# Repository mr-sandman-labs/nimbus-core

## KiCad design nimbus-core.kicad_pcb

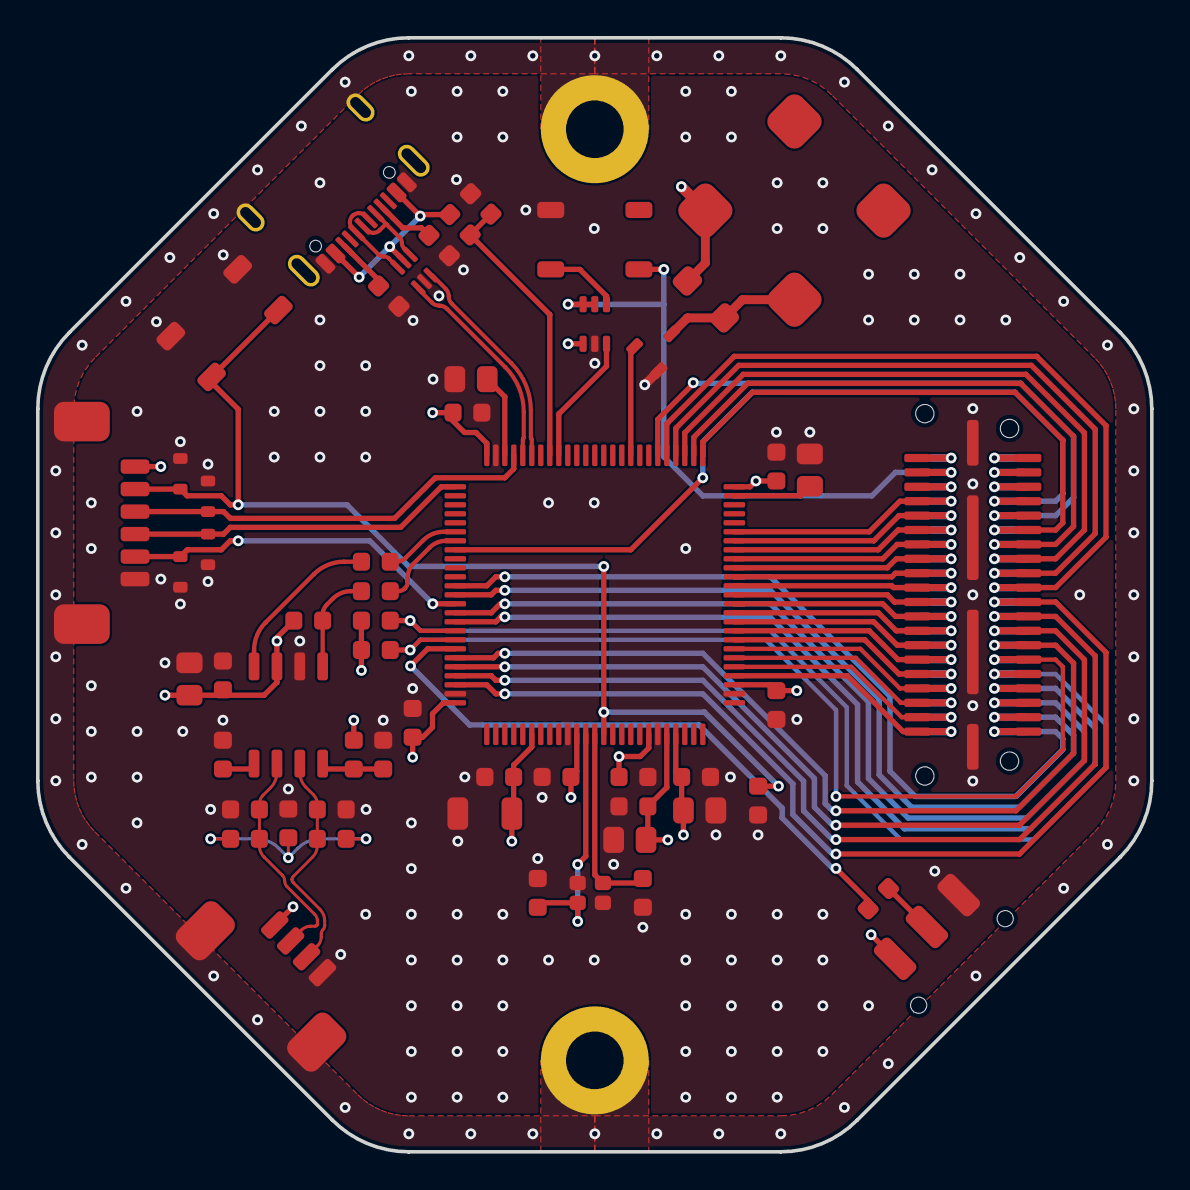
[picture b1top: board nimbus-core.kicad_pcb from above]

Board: 4 copper layers, 61.9 x 61.9 mm, 57 parts (1 on the bottom side), 70 nets.

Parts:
C1, C4, C6, C7, C9, C11, C13, C15, C16, C17, C18, C20, C21: 100nF; C_0603_Density_Nominal
C2, C3: 10pF; C_0603_Density_Nominal
C5, C8: 2.2μF; C_0805_Density_Nominal
C10, C14: 1μF; C_0805_Density_Nominal
C12: 10μF; C_0805_Density_Nominal
C19: 4.7μF; C_1206_Density_Nominal
C22: 4.7nF; C_0603_Density_Nominal
D1: S07M-GS18
D2, D3, D4, D5: D1213A-01T-7
J1: Val**; QTE-020-03-L-D-A
J2: Val**; QSE-020-01-L-D-A
J3: 532614006; 532614004
J4: USB4105-GF-A-120
J5: 532614006
Q1: MMBT2222ALT1G
R1, R4, R5: 10kΩ; R_0603_Density_Nominal
R2, R3: 22.1Ω; R_0603_Density_Nominal
R6, R7: 0Ω; R_0603_Density_Nominal
R8, R9: 60.4Ω; R_0603_Density_Nominal
R10, R11: 1.8kΩ; R_0603_Density_Nominal
R12, R15: 5.1kΩ; R_0603_Density_Nominal
R13: 82kΩ; R_0603_Density_Nominal
R14: 33kΩ; R_0603_Density_Nominal
SW1: PTS647SN50SMTR2 LFS
SW2: JS102011SAQN
U1: LQFP100; STM32F405VGT7
U2: CMT-8504-100-SMT-TR
U3: SOIC-8; SN65HVD233-Q1
U4: TXU0101DCKR
U5: SOT-666-6; USBLC6-2P6
U6: WS2812B
Y1: 25MHz; ABM11AIG-25.000MHZ-4Z-T3

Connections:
+3.3V: C4.1, C6.1, C7.1, C9.1, C10.1, C11.1, C12.1, C13.1, C14.1, C15.1, C16.1, C17.1, C18.1, C19.1, D1.1, J1.5, J1.6, J2.5, J2.6, J3.1, J5.1, R4.1, R5.1, R10.1, R11.1, SW2.1, U1.6 (VBAT), U1.11 (VDD), U1.19 (VDD), U1.21 (VREF+), U1.22 (VDDA), U1.28 (VDD), U1.50 (VDD), U1.75 (VDD), U1.100 (VDD), U2.+, U3.3 (VCC), U4.1 (VCCA)
+5V: J1.3, J1.4, J2.3, J2.4, U4.5 (OE), U4.6 (VCCB), U6.1 (VDD)
/BOOT0: R1.1, U1.94 (BOOT0)
/BUZZER: Q1.1 (B), U1.59 (PD12)
/CAN1_RX: R2.1, U1.81 (CAN1_RX)
/CAN1_TX: R3.1, U1.82 (CAN1_TX)
/CAN_N: C20.1, J3.2, R9.2, U3.6 (CANL)
/CAN_P: C21.1, J3.3, R8.1, U3.7 (CANH)
/CC1: J4.A5 (CC1), R12.1
/CC2: J4.B5 (CC2), R15.1
/I2C1_SCL: J1.31, J2.31, R10.2, U1.92 (I2C1_SCL)
/I2C1_SDA: J1.29, J2.29, R11.2, U1.93 (I2C1_SDA)
/OSC_IN: C2.1, U1.12 (RCC_OSC_IN), Y1.1
/OSC_OUT: C3.1, U1.13 (RCC_OSC_OUT), Y1.3
/PA4: J1.40, J2.40, U1.29 (PA4)
/PB0: J1.28, J2.28, U1.35 (PB0)
/PB1: J1.26, J2.26, U1.36 (PB1)
/PB2: J1.24, J2.24, U1.37 (PB2)
/PB4: J1.35, J2.35, U1.90 (PB4)
/PB5: J1.33, J2.33, U1.91 (PB5)
/PB8: J1.27, J2.27, U1.95 (PB8)
/PB9: J1.25, J2.25, U1.96 (PB9)
/PB12: J1.11, J2.11, U1.51 (PB12)
/PB13: J1.13, J2.13, U1.52 (PB13)
/PB14: J1.15, J2.15, U1.53 (PB14)
/PB15: J1.17, J2.17, U1.54 (PB15)
/PC4: J1.32, J2.32, U1.33 (PC4)
/PC5: J1.30, J2.30, U1.34 (PC5)
/PD2: J1.7, J2.7, U1.83 (PD2)
/PD6: J1.39, J2.39, U1.87 (PD6)
/PD7: J1.37, J2.37, U1.88 (PD7)
/PD8: J1.19, J2.19, U1.55 (PD8)
/PD9: J1.9, J2.9, U1.56 (PD9)
/PE0: J1.23, J2.23, U1.97 (PE0)
/PE1: J1.21, J2.21, U1.98 (PE1)
/PE7: J1.22, J2.22, U1.38 (PE7)
/PE8: J1.20, J2.20, U1.39 (PE8)
/PE9: J1.18, J2.18, U1.40 (PE9)
/PE10: J1.16, J2.16, U1.41 (PE10)
/PE11: J1.14, J2.14, U1.42 (PE11)
/PE12: J1.12, J2.12, U1.43 (PE12)
/PE13: J1.10, J2.10, U1.44 (PE13)
/PE14: J1.8, J2.8, U1.45 (PE14)
/SPI1_MISO: J1.36, J2.36, U1.31 (SPI1_MISO)
/SPI1_MOSI: J1.34, J2.34, U1.32 (SPI1_MOSI)
/SPI1_SCK: J1.38, J2.38, U1.30 (SPI1_SCK)
/STATUS_LED: U1.67 (PA8), U4.3 (A)
/SWCLK: D4.1, J5.4, U1.76 (SYS_JTCK-SWCLK)
/SWDIO: D3.1, J5.3, U1.72 (SYS_JTMS-SWDIO)
/SWO: D5.1, J5.5, U1.89 (SYS_JTDO-SWO)
/USB_CONN_D+: J4.A6 (DP1), J4.B6 (DP2), U5.3 (I/O2)
/USB_CONN_D-: J4.A7 (DN1), J4.B7 (DN2), U5.1 (I/O1)
/USB_D+: U1.71 (USB_OTG_FS_DP), U5.4 (I/O2)
/USB_D-: U1.70 (USB_OTG_FS_DM), U5.6 (I/O1)
/USB_VBUS: R13.2, R14.1, U1.68 (USB_OTG_FS_VBUS)
/VCAP_1: C8.1, U1.49 (VCAP_1)
/VCAP_2: C5.1, U1.73 (VCAP_2)
/~MCU_RESET: C1.1, D2.1, J5.2, SW1.3, SW1.4, U1.14 (NRST)
CHASSIS: J3.MP, J4.SH, J5.MP
GND: C1.2, C2.2, C3.2, C4.2, C5.2, C6.2, C7.2, C8.2, C9.2, C10.2, C11.2, C12.2, C13.2, C14.2, C15.2, C16.2, C17.2, C18.2, C19.2, C20.2, C21.2, C22.2, D2.2, D3.2, D4.2, D5.2, J1.G1, J1.G2, J1.G3, J1.G4, J2.G1, J2.G2, J2.G3, J2.G4, J3.4, J4.A1 (GND), J4.A12 (GND), J4.B1 (GND), J4.B12 (GND), J5.6, Q1.2 (E), R6.1, R7.2, R12.2, R13.1, R15.2, SW1.1, SW1.2, SW2.3, U1.10 (VSS), U1.20 (VSSA), U1.27 (VSS), U1.74 (VSS), U1.99 (VSS), U3.2 (GND), U4.2 (GND), U5.5 (VBUS), U6.3 (VSS), Y1.2, Y1.4
unnamed: C22.1, R8.2, R9.1
unnamed: D1.2, Q1.3 (C), U2.-
unnamed: R1.2, SW2.2
unnamed: R6.2, U3.5 (LBK)
unnamed: R5.2, R7.1, U3.8 (RS)
unnamed: R2.2, U3.4 (RXD)
unnamed: R3.2, R4.2, U3.1 (TXD)
unnamed: U4.4 (BY), U6.4 (DIN)
VBAT: J1.1, J1.2, J2.1, J2.2
VUSB: J4.A4 (VBUS), J4.A9 (VBUS), J4.B4 (VBUS), J4.B9 (VBUS), R14.2, U5.2 (GND)

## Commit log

2025-12-14 Add kicad-library
2025-12-14 Initialize project
2025-12-14 Update to latest library
2025-12-14 Include kicad-library in the project
2025-12-14 Update library
2025-12-14 Import shematic
2025-12-14 Import rules from AISLER
2025-12-14 Place PCB and Microcontroller
2025-12-14 Place USB, add holes around PCB edge
2025-12-15 Connect bottom passthrough connector with top one both in schematic and PCB
2025-12-15 Change PCB color to black
2025-12-15 Place connectors around PCB edge
2025-12-15 Add TVS diodes to SWD connector
2025-12-16 Switched PCB from round to octagonal
2025-12-16 Adjust default class settings to allow differential pair routing
2025-12-16 Add first connections to passtrough, will likely need some iteration
2025-12-16 Add 100 Ohm differential pair
2025-12-17 Shift passthrough pinout by 1 to insert another pin
2025-12-17 Moved passthrough connector to allow for connections on far the far side
2025-12-18 Rename all passthrough pins to their corresponding MCU pin name, fix typo on SPI pins
2025-12-18 Updated kicad-library
2025-12-19 Update kicad-library
2025-12-19 Update schematic symbols using the "ic" library reference to "integrated_semiconductor"
2025-12-21 Remove 6 GPIOs to add VBAT, +5V, +3.3V power rails in the passthrough connector
2025-12-22 Added RGB LED
2025-12-22 Add reset tactile switch, CAN routing and BOOT0 SPDT switch
2025-12-23 Improve CAN driver layout to be more compact
2025-12-23 Position BOOT0 SPDT switch, refill zones and add stitching vias for GND
2025-12-23 Change license from GPL 3.0 to CERN-OHL-S
2025-12-29 Use new worksheet template
2026-01-01 Update worksheet template in PCB
2026-01-01 Add title to worksheet on PCB
2026-01-02 Add github workflow to generate PCB images
2026-01-02 Fix -height typo
2026-01-02 Switch to debian-latest image, break down commands for readability
2026-01-02 Switch back to ubuntu-latest, but add kicad PPA
2026-01-02 Install a slimmed down version of kicad to improve speed, fix error in committing the wrong files
2026-01-02 Remove kicad-common
2026-01-02 Test commit for pipeline
2026-01-02 Update PCB images
2026-01-02 Add recursive submodules to workflow
2026-01-02 Rename board images updater to run only on file change
2026-01-02 Commit first draft of a releaser for testing
2026-01-02 Add fonts to both workflows, attempt fix in BOM generation for the releaser
2026-01-02 Add netlist and interactive HTML BOM generation
2026-01-02 Install InteractiveHtmlBom python package
2026-01-02 Simplify dependency step, run HTML BOM generation in virtual framebuffer
2026-01-02 Replace date and revision with variables
2026-01-02 Add revision extraction from project
2026-01-02 Add release step
2026-01-02 Fix revision scoping issue
2026-01-02 Add recursive option to final zip
2026-01-02 Fix login issue, add renaming of PCB PDF output
2026-01-02 Fix missing render in workflow
2026-01-02 Remove revision validation step, GitHub creates a tag for each release, so it won't create another release with the same revision number.
2026-01-03 Add ability to update board images via GitHub UI
2026-01-04 Add User.Drawings layer to PCB PDF
2026-01-04 Change revision from 1.0.0 to 1.0.1
2026-01-04 Update board images
2026-01-04 Change PCB color from black to green

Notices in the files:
parts and their libraries:
LICENSE: CERN-OHL-S
